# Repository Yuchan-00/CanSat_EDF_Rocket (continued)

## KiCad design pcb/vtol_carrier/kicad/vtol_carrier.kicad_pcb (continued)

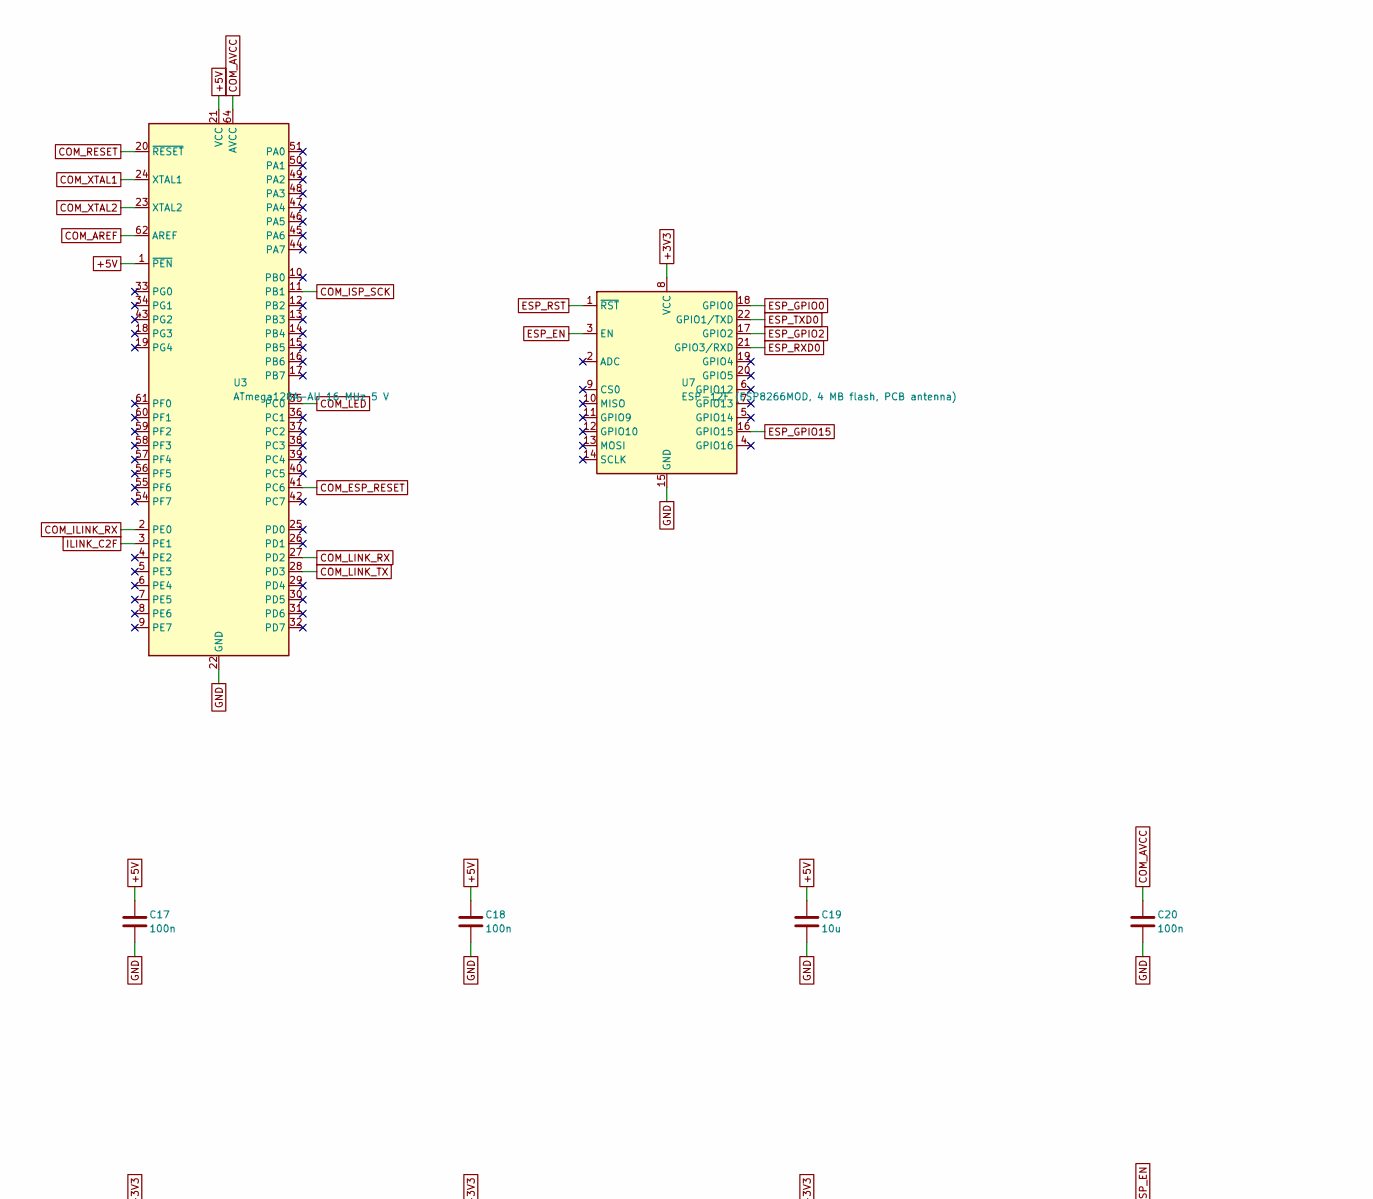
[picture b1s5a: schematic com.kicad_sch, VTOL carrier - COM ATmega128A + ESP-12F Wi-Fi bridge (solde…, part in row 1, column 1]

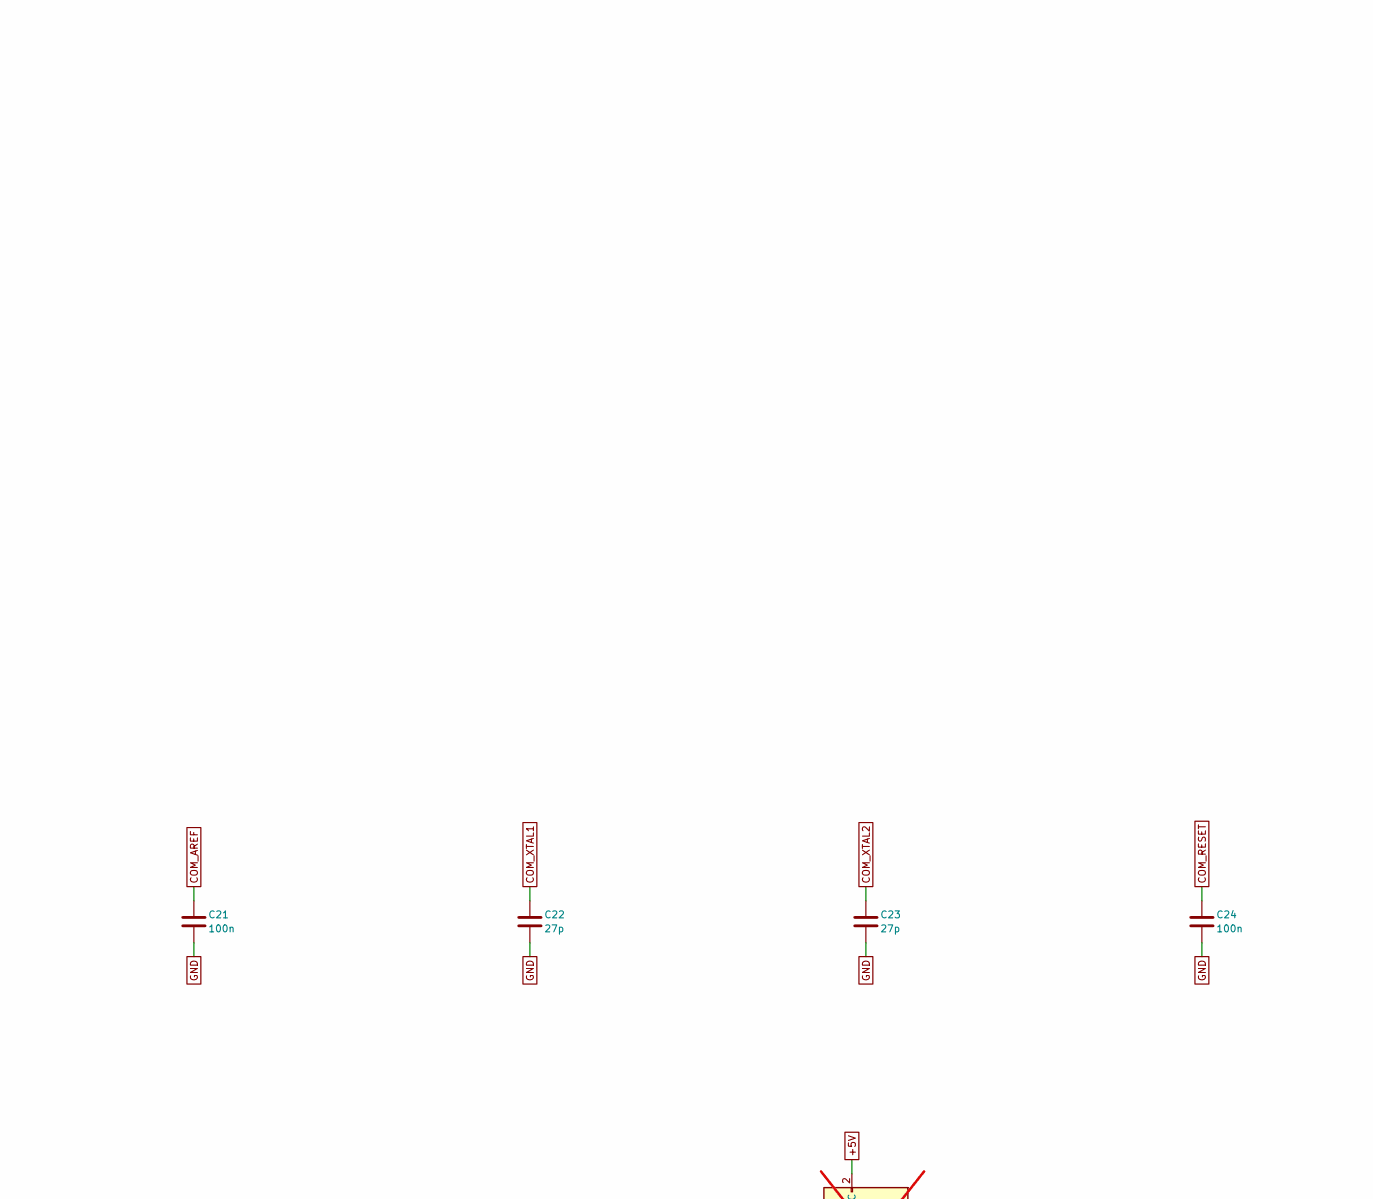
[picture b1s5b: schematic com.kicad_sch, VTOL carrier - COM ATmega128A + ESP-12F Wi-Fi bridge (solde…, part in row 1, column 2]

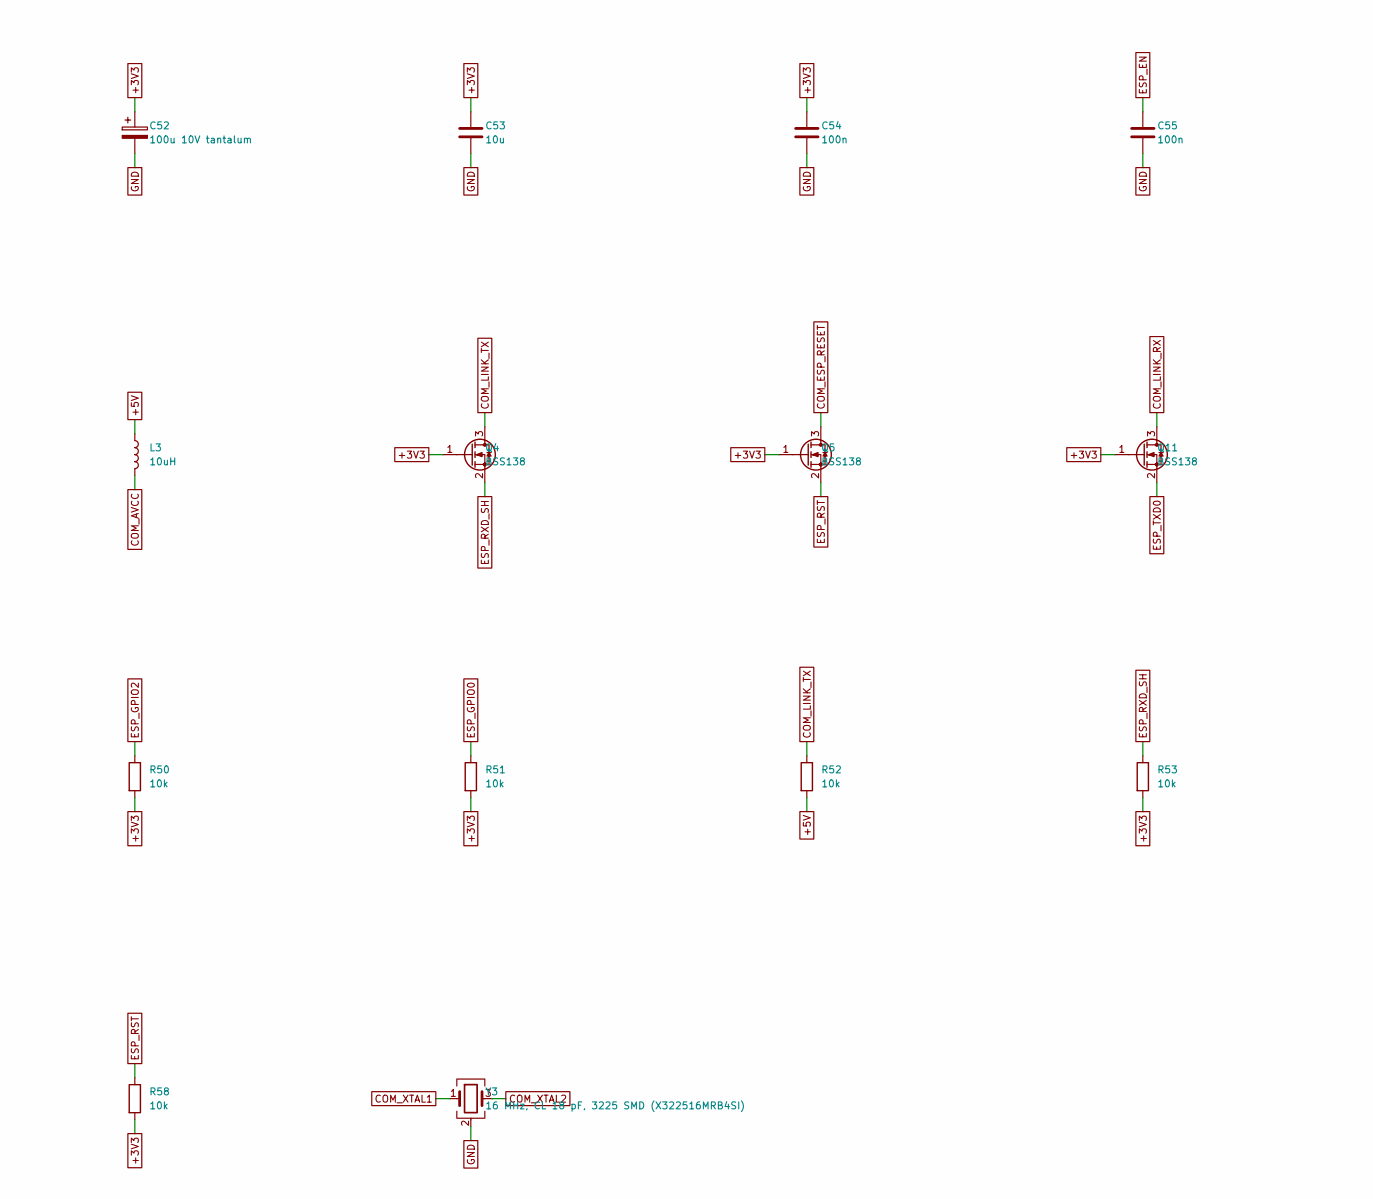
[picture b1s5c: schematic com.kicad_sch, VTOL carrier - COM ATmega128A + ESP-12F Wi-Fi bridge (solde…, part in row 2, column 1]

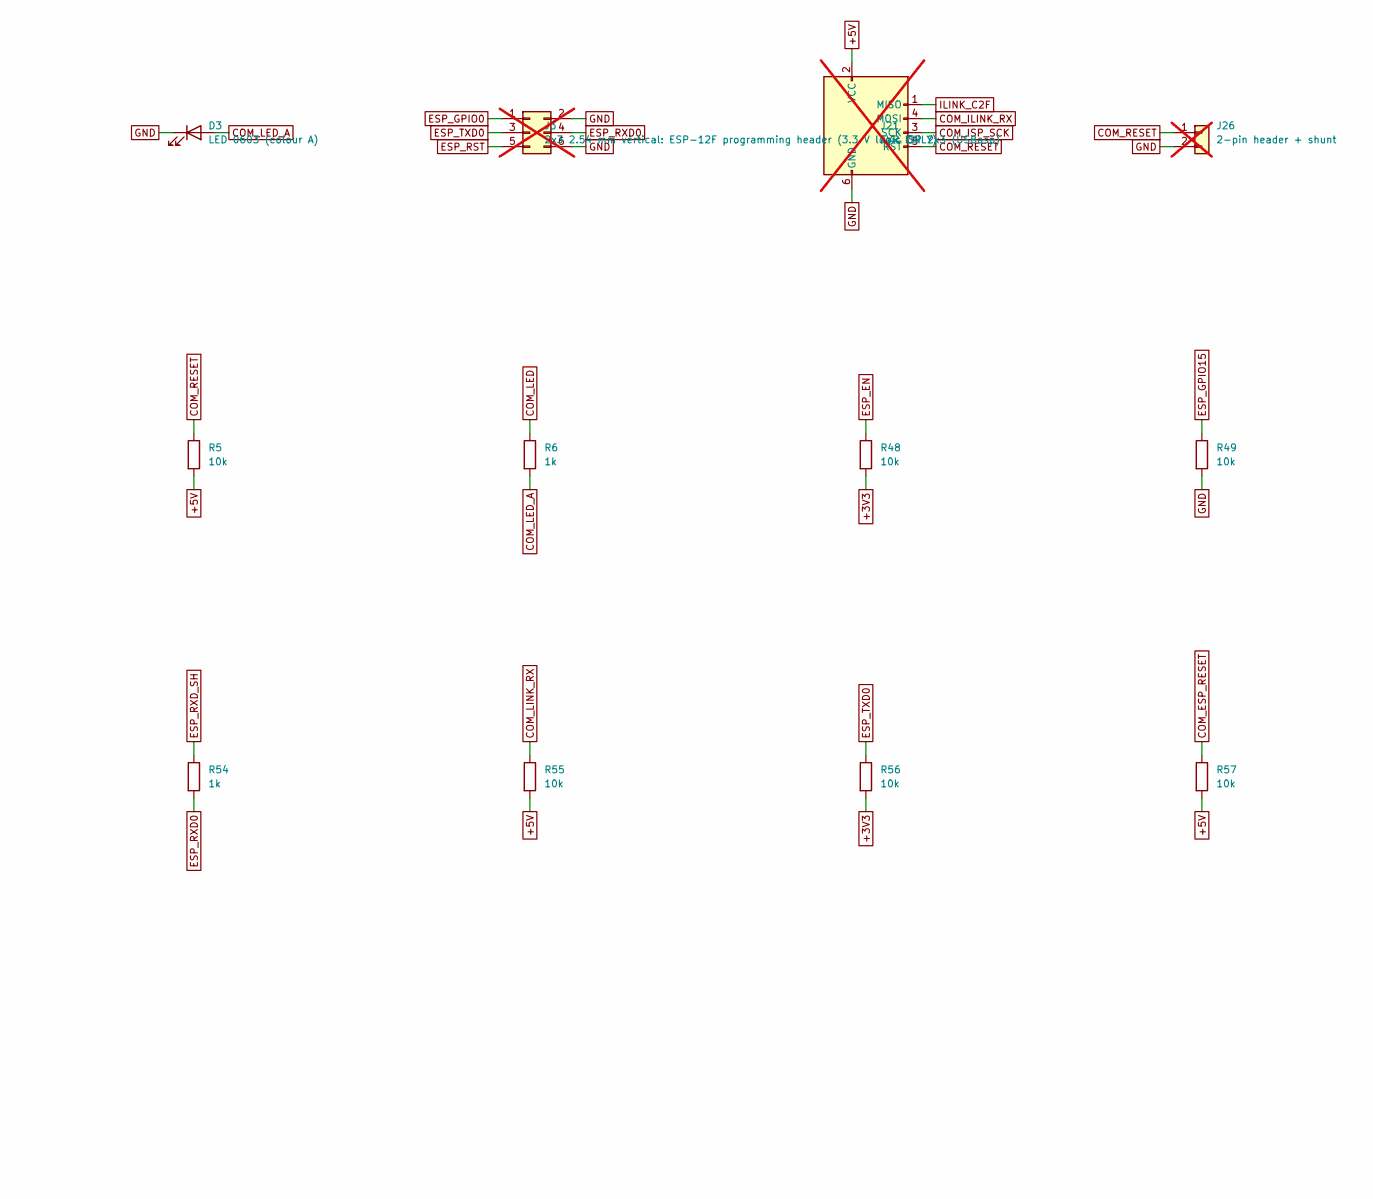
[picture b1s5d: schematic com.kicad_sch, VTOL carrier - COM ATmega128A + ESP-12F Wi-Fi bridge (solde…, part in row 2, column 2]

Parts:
C17, C18, C20, C54: 100n; C_0402_1005Metric
C19, C53: 10u; C_0805_2012Metric
C21, C24, C55: 100n; C_0603_1608Metric
C22, C23: 27p; C_0402_1005Metric
C52: 100u 10V tantalum; CP_EIA-3528-21_Kemet-B
D3: LED 0603 (colour A); LED_0603_1608Metric
J3: 2x3 2.54 mm vertical: ESP-12F programming header 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; PinHeader_2x03_P2.54mm_Vertical; not fitted
J21: AVR ISP 2x3 (USBasp); PinHeader_2x03_P2.54mm_Vertical; not fitted
J26: 2-pin header + shunt; PinHeader_1x02_P2.54mm_Vertical; not fitted
L3: 10uH; L_0805_2012Metric
Q4, Q5, Q11: BSS138; SOT-23
R5, R48, R49, R50, R51, R52, R53, R55, R56, R57, R58: 10k; R_0603_1608Metric
R6, R54: 1k; R_0603_1608Metric
U3: ATmega128A-AU 16 MHz 5 V; TQFP-64_14x14mm_P0.8mm
U7: ESP-12F (ESP8266MOD, 4 MB flash, PCB antenna); ESP-12E
Y3: 16 MHz, CL 18 pF, 3225 SMD (X322516MRB4SI); Crystal_SMD_3225-4Pin_3.2x2.5mm

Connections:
+3V3: C52.1, C53.1, C54.1, Q4.1 (G), Q5.1 (G), Q11.1 (G), R48.2, R50.2, R51.2, R53.2, R56.2, R58.2, U7.8 (VCC); also elsewhere on the board
+5V: C17.1, C18.1, C19.1, J21.2 (VCC), L3.1, R5.2, R52.2, R55.2, R57.2, U3.1 (~PEN), U3.21 (VCC), U3.52 (VCC); also elsewhere on the board
COM_AREF: C21.1, U3.62 (AREF)
COM_AVCC: C20.1, L3.2, U3.64 (AVCC)
COM_ESP_RESET: Q5.3 (D), R57.1, U3.41 (PC6)
COM_ILINK_RX: J21.4 (MOSI), U3.2 (PE0); also elsewhere on the board
COM_ISP_SCK: J21.3 (SCK), U3.11 (PB1)
COM_LED: R6.1, U3.35 (PC0)
COM_LED_A: D3.2 (A), R6.2
COM_LINK_RX: Q11.3 (D), R55.1, U3.27 (PD2)
COM_LINK_TX: Q4.3 (D), R52.1, U3.28 (PD3)
COM_RESET: C24.1, J21.5 (~RST), J26.1, R5.1, U3.20 (~RESET)
COM_XTAL1: C22.1, U3.24 (XTAL1), Y3.1
COM_XTAL2: C23.1, U3.23 (XTAL2), Y3.3
ESP_EN: C55.1, R48.1, U7.3 (EN)
ESP_GPIO0: J3.1, R51.1, U7.18 (GPIO0)
ESP_GPIO2: R50.1, U7.17 (GPIO2)
ESP_GPIO15: R49.1, U7.16 (GPIO15)
ESP_RST: J3.5, Q5.2 (S), R58.1, U7.1 (~RST)
ESP_RXD0: J3.4, R54.2, U7.21 (GPIO3/RXD)
ESP_RXD_SH: Q4.2 (S), R53.1, R54.1
ESP_TXD0: J3.3, Q11.2 (S), R56.1, U7.22 (GPIO1/TXD)
GND: C17.2, C18.2, C19.2, C20.2, C21.2, C22.2, C23.2, C24.2, C52.2, C53.2, C54.2, C55.2, D3.1 (K), J3.2, J3.6, J21.6 (GND), J26.2, R49.2, U3.22 (GND), U3.53 (GND), U3.63 (GND), U7.15 (GND), Y3.2 (G), Y3.4 (G); also elsewhere on the board
ILINK_C2F: J21.1 (MISO), U3.3 (PE1); also elsewhere on the board

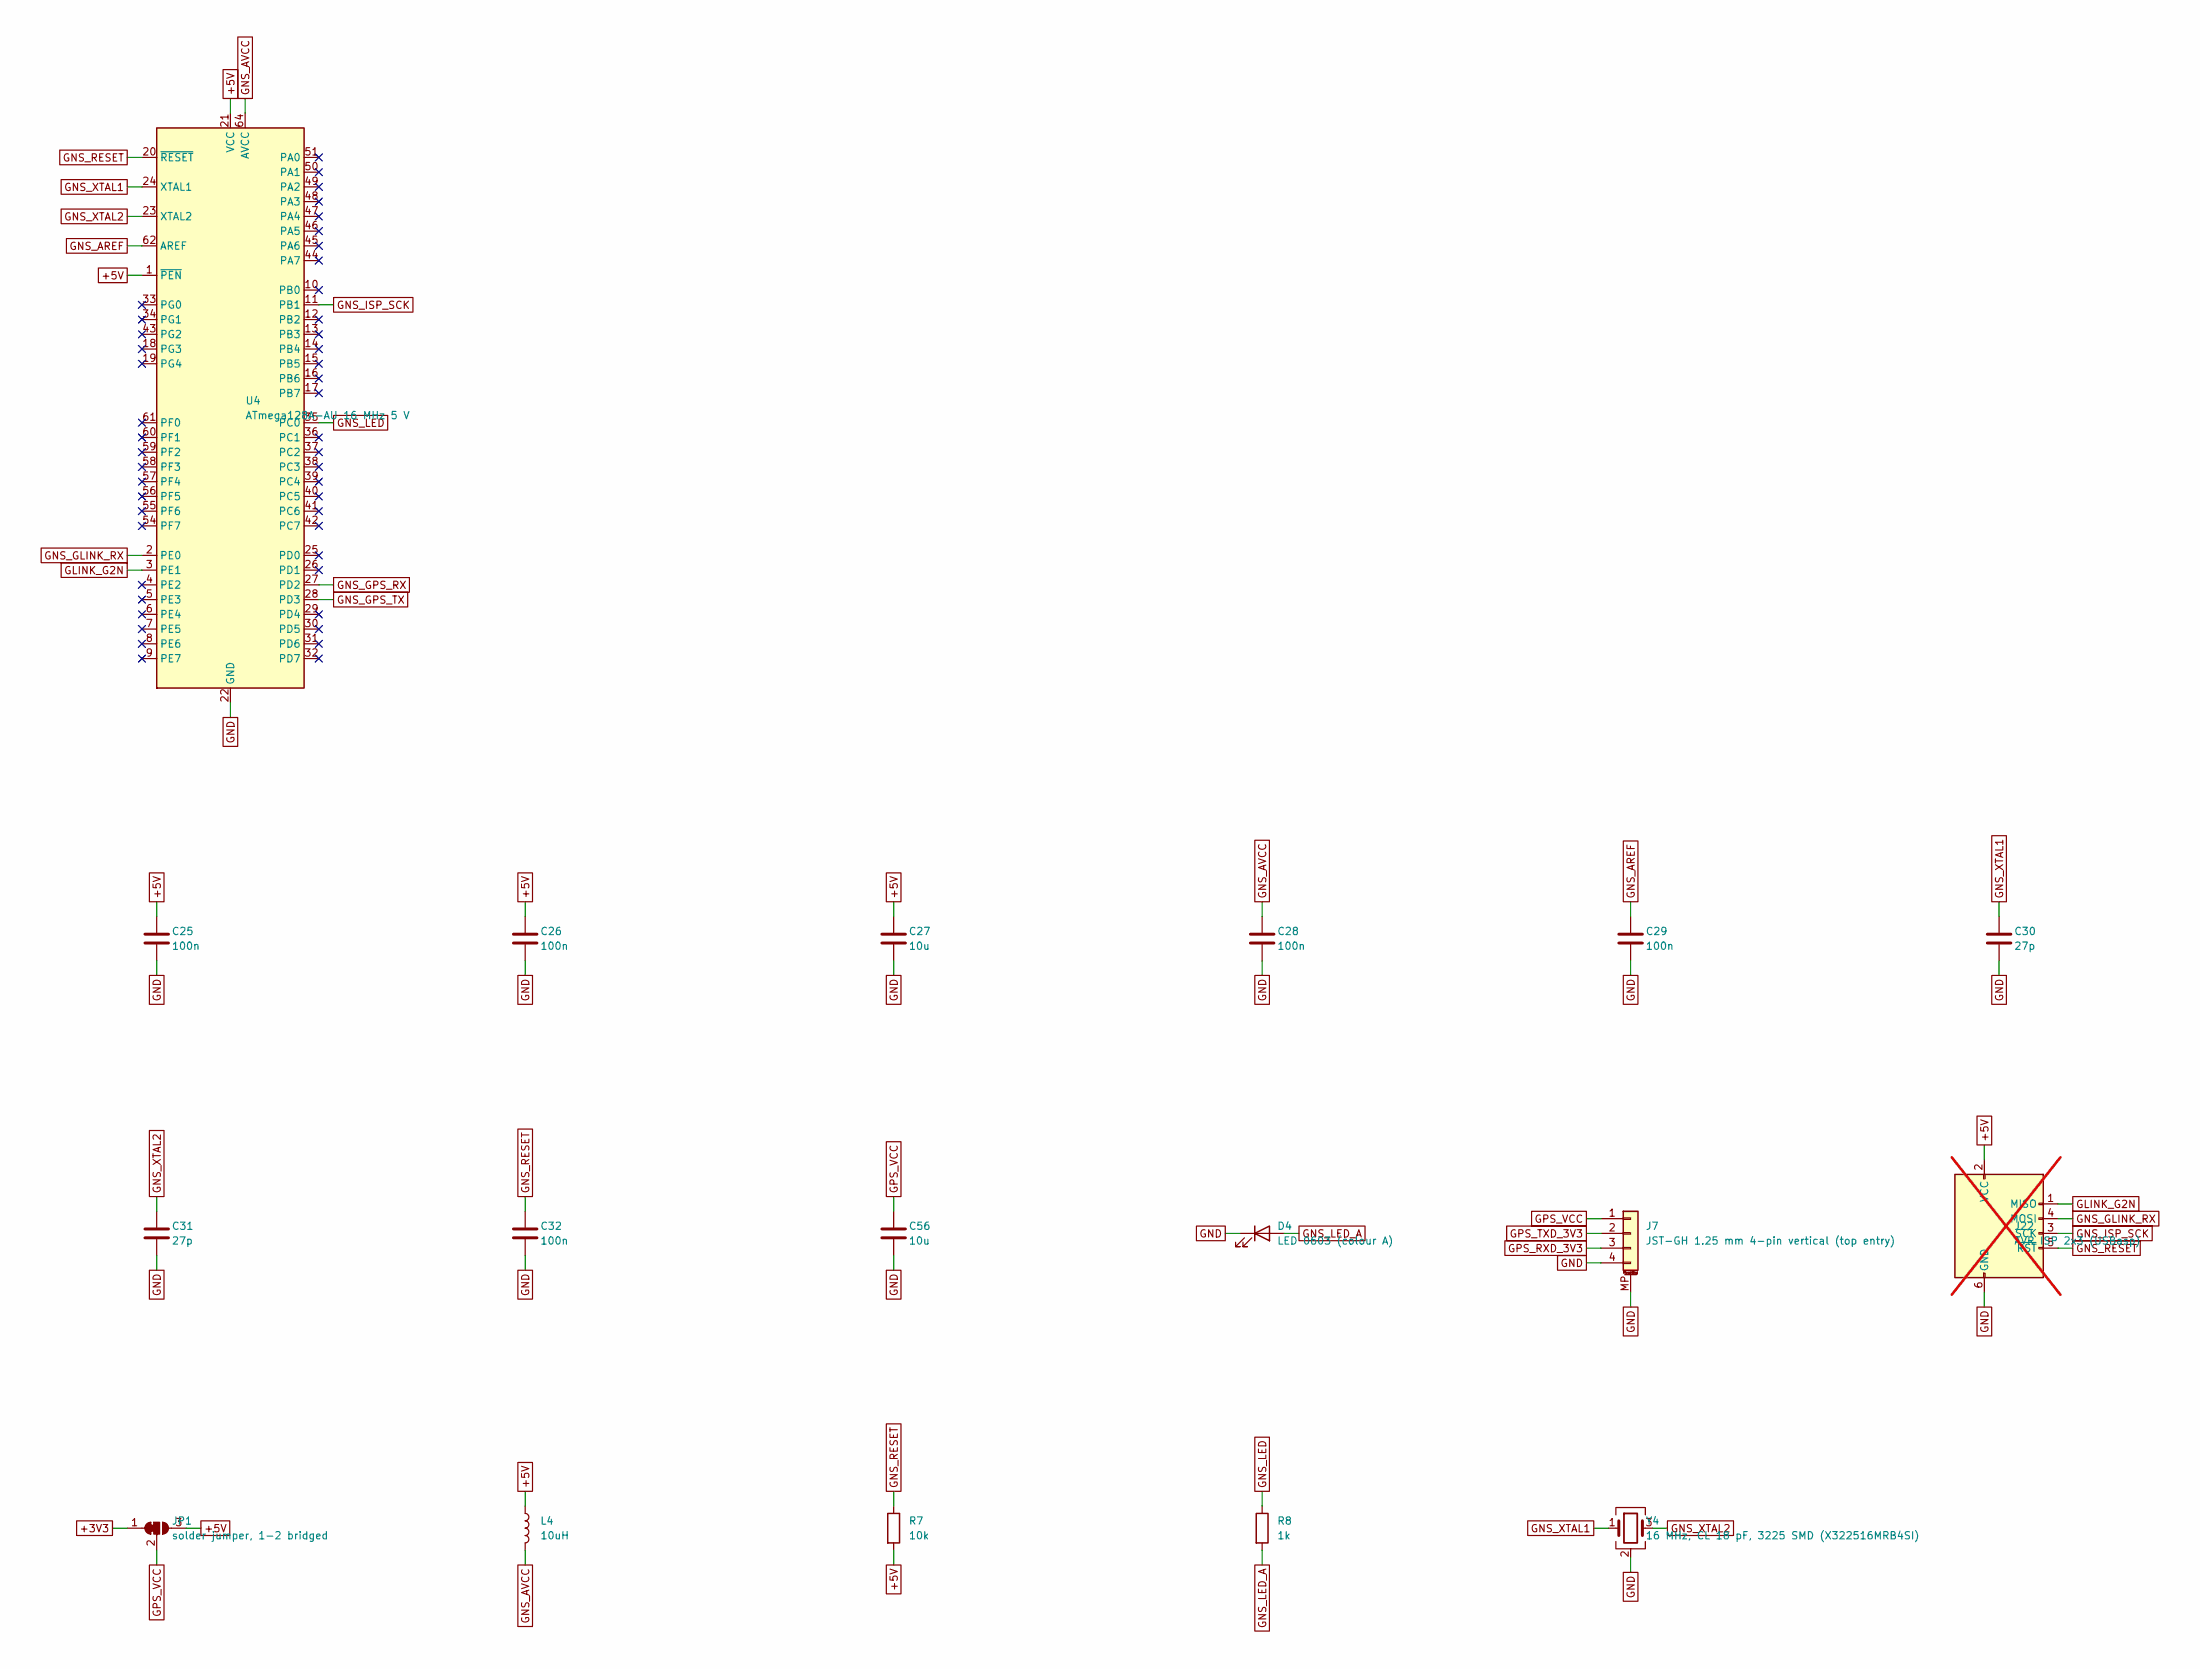
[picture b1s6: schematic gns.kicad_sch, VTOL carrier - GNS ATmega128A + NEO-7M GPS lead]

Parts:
C25, C26, C28: 100n; C_0402_1005Metric
C27, C56: 10u; C_0805_2012Metric
C29, C32: 100n; C_0603_1608Metric
C30, C31: 27p; C_0402_1005Metric
D4: LED 0603 (colour A); LED_0603_1608Metric
J7: JST-GH 1.25 mm 4-pin vertical (top entry); JST_GH_BM04B-GHS-TBT_1x04-1MP_P1.25mm_Vertical
J22: AVR ISP 2x3 (USBasp); PinHeader_2x03_P2.54mm_Vertical; not fitted
JP1: solder jumper, 1-2 bridged; SolderJumper-3_P1.3mm_Bridged12_RoundedPad1.0x1.5mm
L4: 10uH; L_0805_2012Metric
R7: 10k; R_0603_1608Metric
R8: 1k; R_0603_1608Metric
U4: ATmega128A-AU 16 MHz 5 V; TQFP-64_14x14mm_P0.8mm
Y4: 16 MHz, CL 18 pF, 3225 SMD (X322516MRB4SI); Crystal_SMD_3225-4Pin_3.2x2.5mm

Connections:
+3V3: JP1.1 (A); also elsewhere on the board
+5V: C25.1, C26.1, C27.1, J22.2 (VCC), JP1.3 (B), L4.1, R7.2, U4.1 (~PEN), U4.21 (VCC), U4.52 (VCC); also elsewhere on the board
GLINK_G2N: J22.1 (MISO), U4.3 (PE1); also elsewhere on the board
GND: C25.2, C26.2, C27.2, C28.2, C29.2, C30.2, C31.2, C32.2, C56.2, D4.1 (K), J7.4, J7.MP (MountPin), J22.6 (GND), U4.22 (GND), U4.53 (GND), U4.63 (GND), Y4.2 (G), Y4.4 (G); also elsewhere on the board
GNS_AREF: C29.1, U4.62 (AREF)
GNS_AVCC: C28.1, L4.2, U4.64 (AVCC)
GNS_GLINK_RX: J22.4 (MOSI), U4.2 (PE0); also elsewhere on the board
GNS_GPS_RX: U4.27 (PD2); also elsewhere on the board
GNS_GPS_TX: U4.28 (PD3); also elsewhere on the board
GNS_ISP_SCK: J22.3 (SCK), U4.11 (PB1)
GNS_LED: R8.1, U4.35 (PC0)
GNS_LED_A: D4.2 (A), R8.2
GNS_RESET: C32.1, J22.5 (~RST), R7.1, U4.20 (~RESET)
GNS_XTAL1: C30.1, U4.24 (XTAL1), Y4.1
GNS_XTAL2: C31.1, U4.23 (XTAL2), Y4.3
GPS_RXD_3V3: J7.3; also elsewhere on the board
GPS_TXD_3V3: J7.2; also elsewhere on the board
GPS_VCC: C56.1, J7.1, JP1.2 (C)

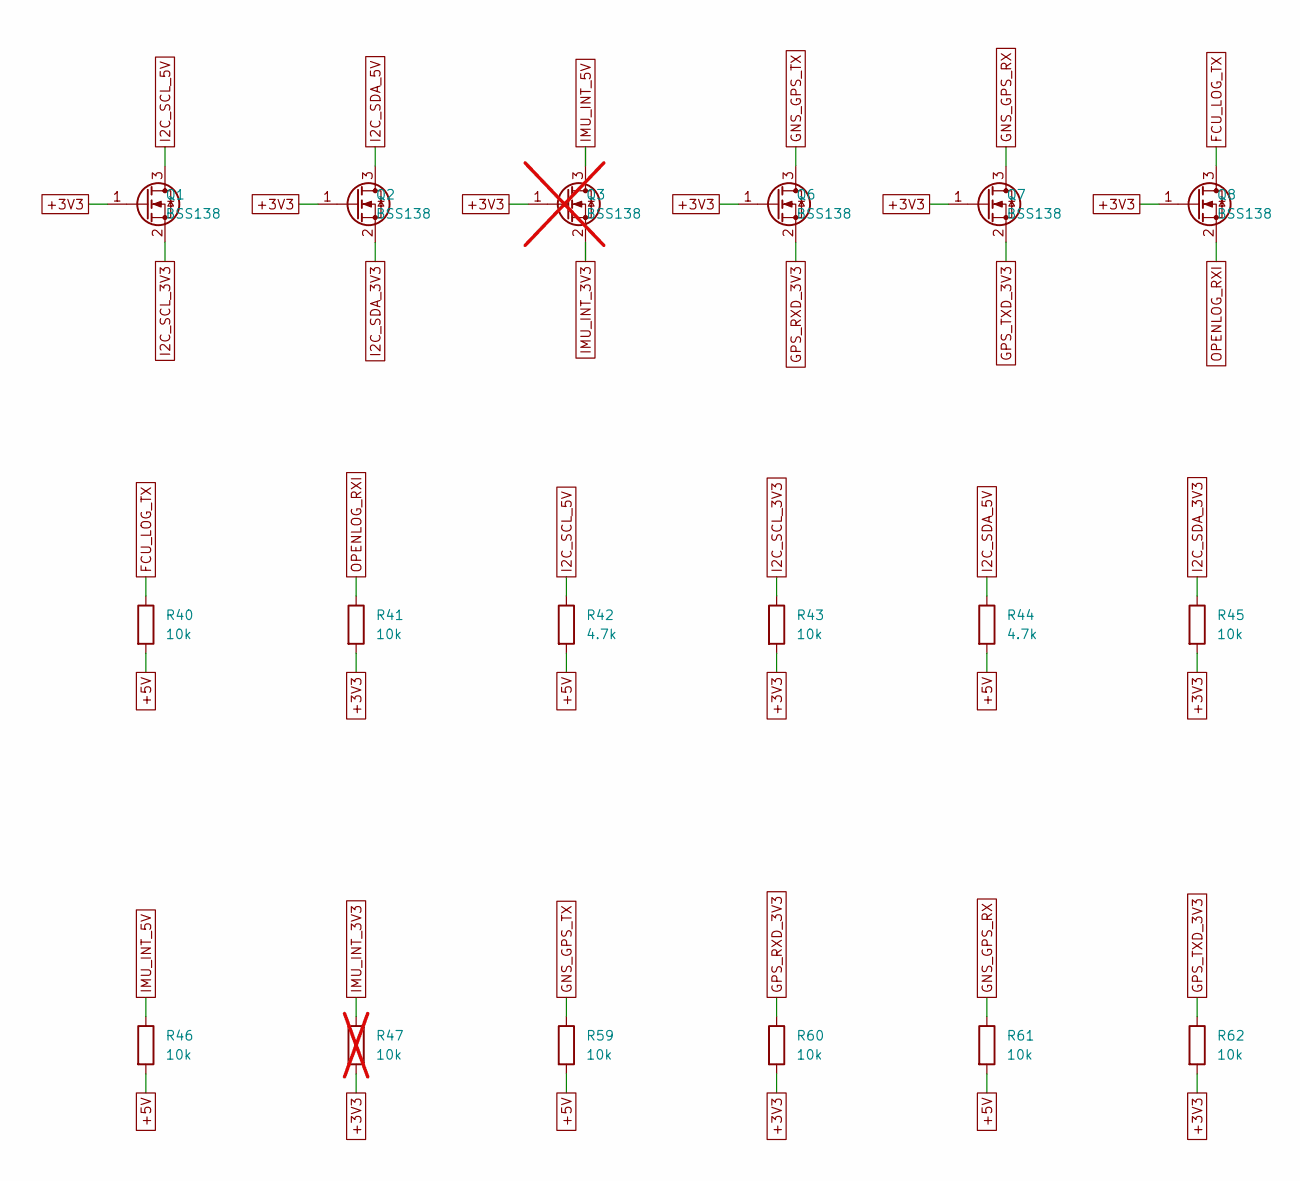
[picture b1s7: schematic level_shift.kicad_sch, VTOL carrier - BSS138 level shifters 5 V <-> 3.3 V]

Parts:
Q1, Q2, Q6, Q7, Q8: BSS138; SOT-23
Q3: BSS138; SOT-23; not fitted
R40, R41, R43, R45, R46, R59, R60, R61, R62: 10k; R_0603_1608Metric
R42, R44: 4.7k; R_0603_1608Metric
R47: 10k; R_0603_1608Metric; not fitted

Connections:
+3V3: Q1.1 (G), Q2.1 (G), Q3.1 (G), Q6.1 (G), Q7.1 (G), Q8.1 (G), R41.2, R43.2, R45.2, R47.2, R60.2, R62.2; also elsewhere on the board
+5V: R40.2, R42.2, R44.2, R46.2, R59.2, R61.2; also elsewhere on the board
FCU_LOG_TX: Q8.3 (D), R40.1; also elsewhere on the board
GNS_GPS_RX: Q7.3 (D), R61.1; also elsewhere on the board
GNS_GPS_TX: Q6.3 (D), R59.1; also elsewhere on the board
GPS_RXD_3V3: Q6.2 (S), R60.1; also elsewhere on the board
GPS_TXD_3V3: Q7.2 (S), R62.1; also elsewhere on the board
I2C_SCL_3V3: Q1.2 (S), R43.1; also elsewhere on the board
I2C_SCL_5V: Q1.3 (D), R42.1; also elsewhere on the board
I2C_SDA_3V3: Q2.2 (S), R45.1; also elsewhere on the board
I2C_SDA_5V: Q2.3 (D), R44.1; also elsewhere on the board
IMU_INT_3V3: Q3.2 (S), R47.1; also elsewhere on the board
IMU_INT_5V: Q3.3 (D), R46.1; also elsewhere on the board
OPENLOG_RXI: Q8.2 (S), R41.1; also elsewhere on the board

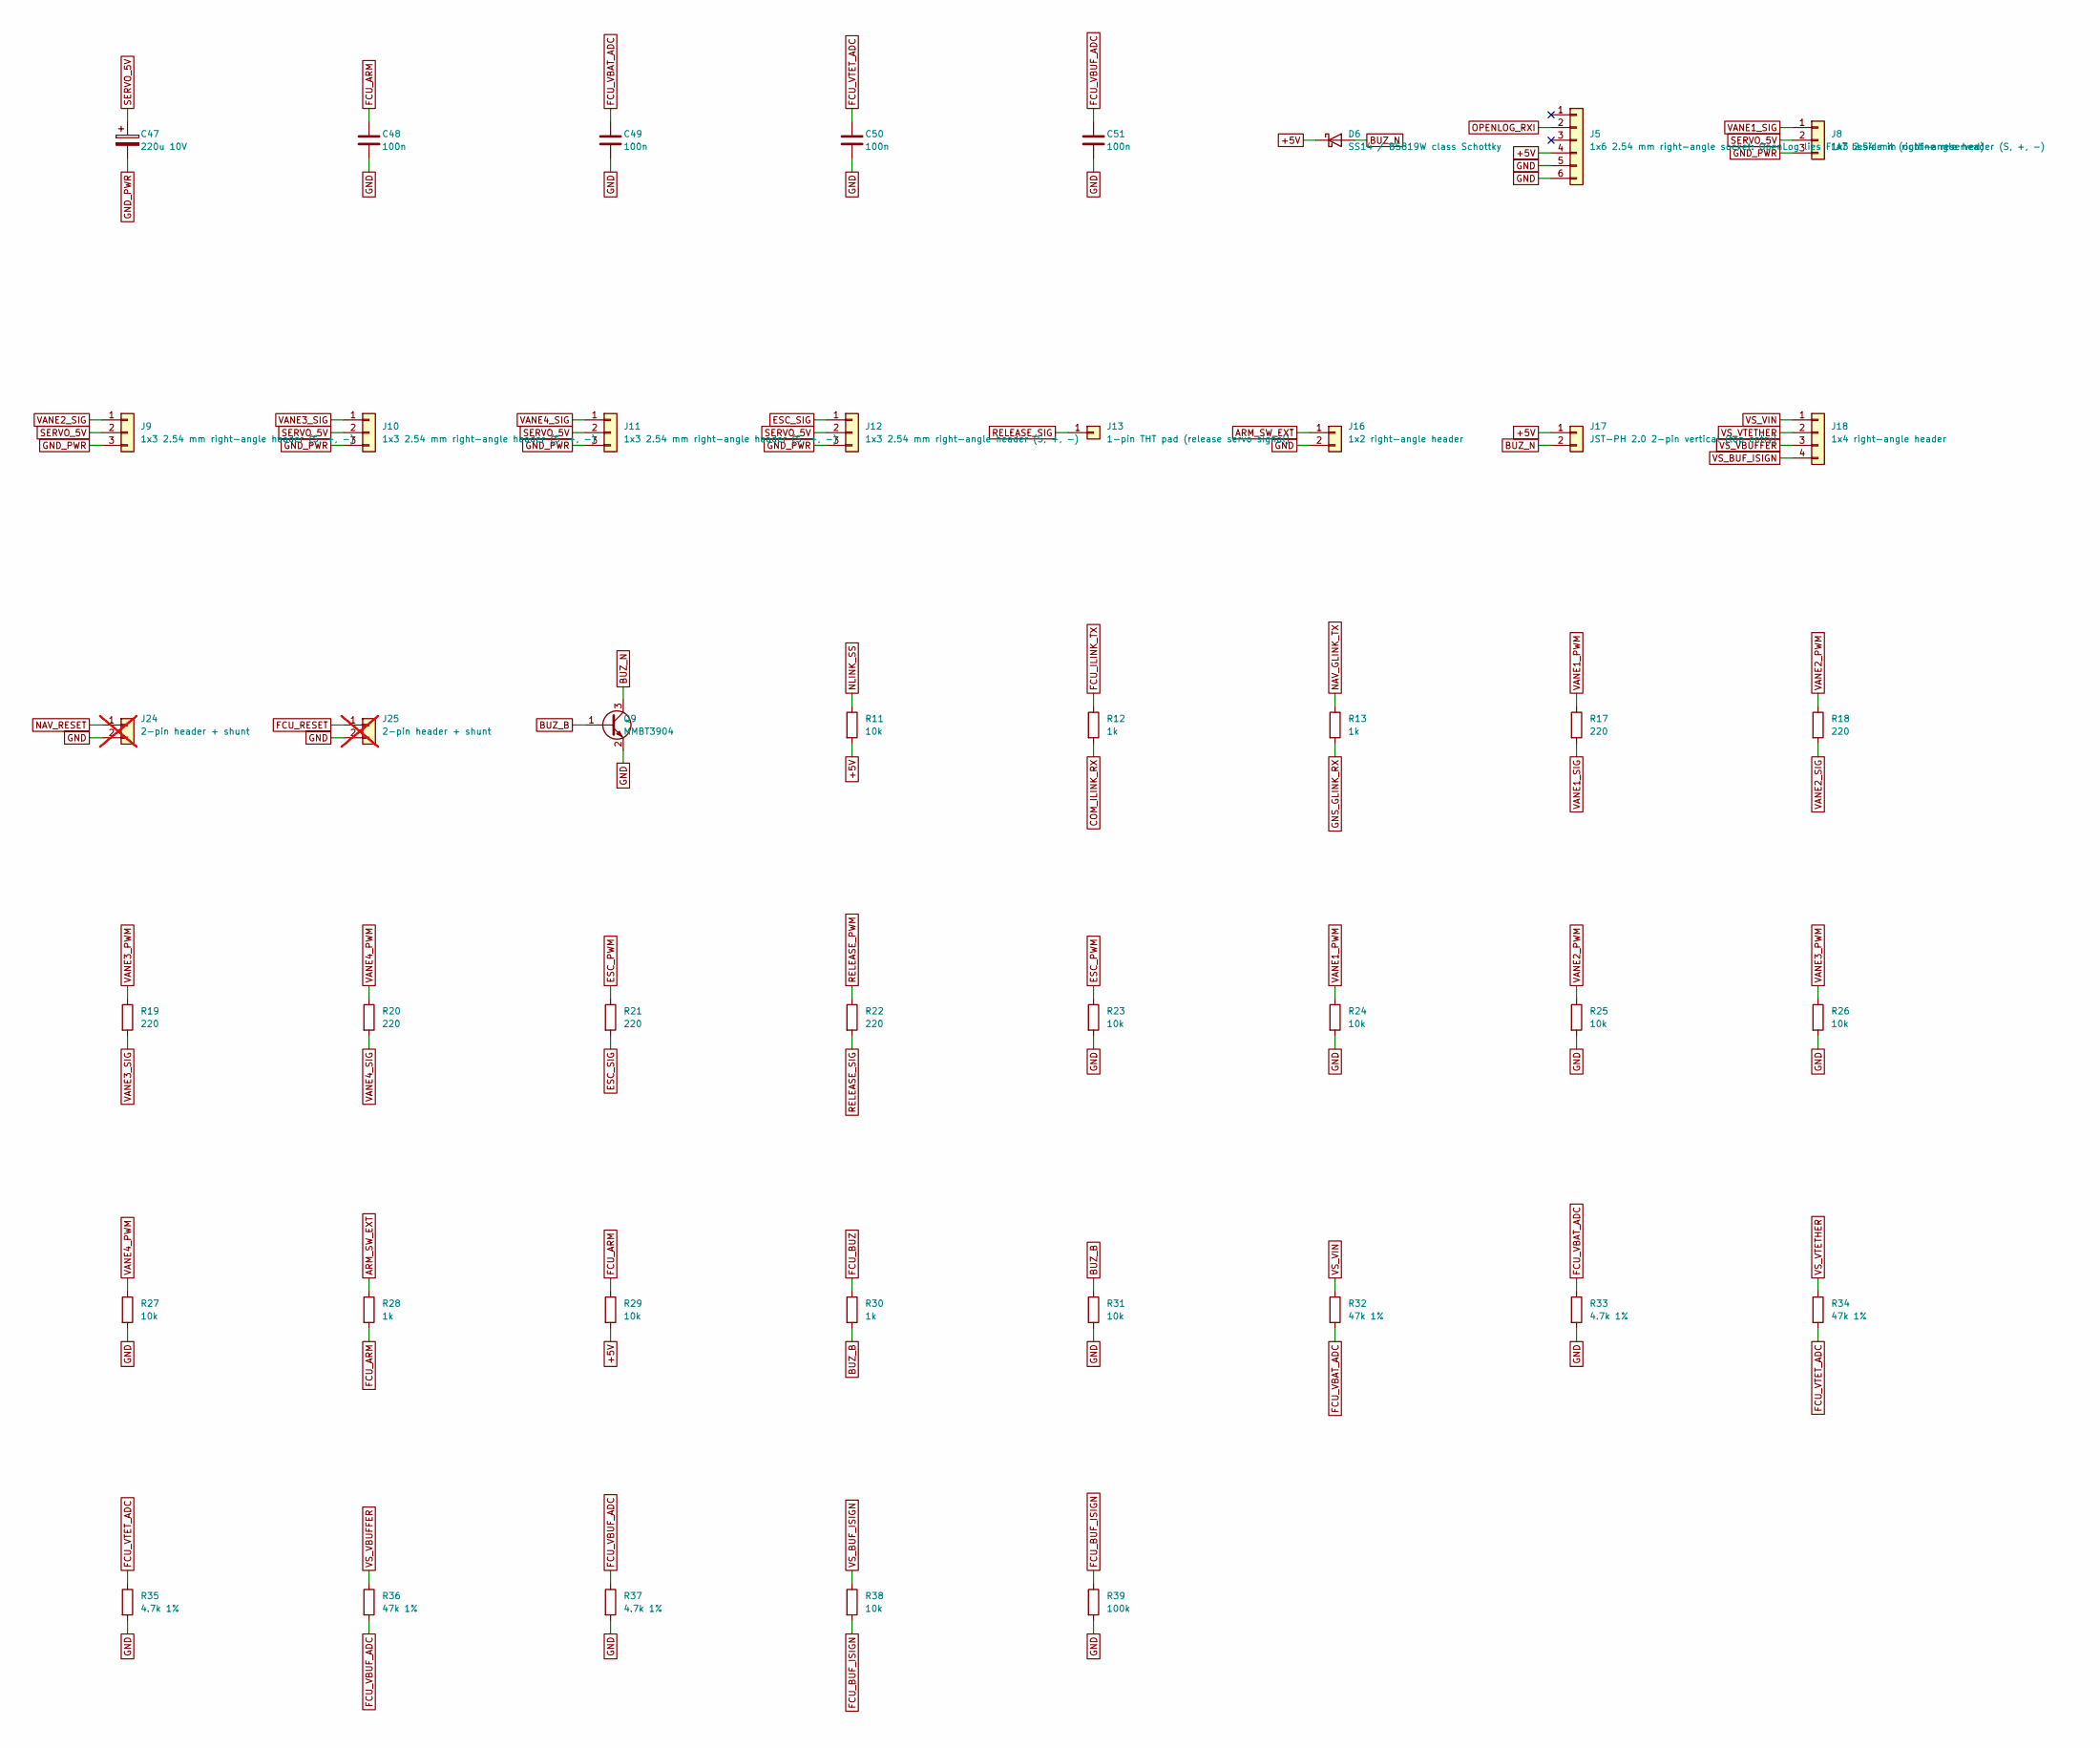
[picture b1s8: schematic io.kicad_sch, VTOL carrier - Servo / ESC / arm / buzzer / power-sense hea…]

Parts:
C47: 220u 10V; CP_Elec_6.3x5.4
C48, C49, C50, C51: 100n; C_0603_1608Metric
D6: SS14 / B5819W class Schottky; D_SOD-123
J5: 1x6 2.54 mm right-angle socket: OpenLog lies FLAT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; PinSocket_1x06_P2.54mm_Horizontal
J8, J9, J10, J11, J12: 1x3 2.54 mm right-angle header (S, +, -); PinHeader_1x03_P2.54mm_Horizontal
J13: 1-pin THT pad (release servo signal); TestPoint_THTPad_D2.0mm_Drill1.0mm
J16: 1x2 right-angle header; PinHeader_1x02_P2.54mm_Horizontal
J17: JST-PH 2.0 2-pin vertical (top entry); JST_PH_B2B-PH-K_1x02_P2.00mm_Vertical
J18: 1x4 right-angle header; PinHeader_1x04_P2.54mm_Horizontal
J24, J25: 2-pin header + shunt; PinHeader_1x02_P2.54mm_Vertical; not fitted
Q9: MMBT3904; SOT-23
R11, R23, R24, R25, R26, R27, R29, R31, R38: 10k; R_0603_1608Metric
R12, R13, R28, R30: 1k; R_0603_1608Metric
R17, R18, R19, R20, R21, R22: 220; R_0603_1608Metric
R32, R34, R36: 47k 1%; R_0603_1608Metric
R33, R35, R37: 4.7k 1%; R_0603_1608Metric
R39: 100k; R_0603_1608Metric

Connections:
+5V: D6.1 (K), J5.4, J17.1, R11.2, R29.2; also elsewhere on the board
ARM_SW_EXT: J16.1, R28.1
BUZ_B: Q9.1 (B), R30.2, R31.1
BUZ_N: D6.2 (A), J17.2, Q9.3 (C)
COM_ILINK_RX: R12.2; also elsewhere on the board
ESC_PWM: R21.1, R23.1; also elsewhere on the board
ESC_SIG: J12.1, R21.2
FCU_ARM: C48.1, R28.2, R29.1; also elsewhere on the board
FCU_BUF_ISIGN: R38.2, R39.1; also elsewhere on the board
FCU_BUZ: R30.1; also elsewhere on the board
FCU_ILINK_TX: R12.1; also elsewhere on the board
FCU_RESET: J25.1; also elsewhere on the board
FCU_VBAT_ADC: C49.1, R32.2, R33.1; also elsewhere on the board
FCU_VBUF_ADC: C51.1, R36.2, R37.1; also elsewhere on the board
FCU_VTET_ADC: C50.1, R34.2, R35.1; also elsewhere on the board
GND: C48.2, C49.2, C50.2, C51.2, J5.5, J5.6, J16.2, J24.2, J25.2, Q9.2 (E), R23.2, R24.2, R25.2, R26.2, R27.2, R31.2, R33.2, R35.2, R37.2, R39.2; also elsewhere on the board
GND_PWR: C47.2, J8.3, J9.3, J10.3, J11.3, J12.3; also elsewhere on the board
GNS_GLINK_RX: R13.2; also elsewhere on the board
NAV_GLINK_TX: R13.1; also elsewhere on the board
NAV_RESET: J24.1; also elsewhere on the board
NLINK_SS: R11.1; also elsewhere on the board
OPENLOG_RXI: J5.2; also elsewhere on the board
RELEASE_PWM: R22.1; also elsewhere on the board
RELEASE_SIG: J13.1, R22.2
SERVO_5V: C47.1, J8.2, J9.2, J10.2, J11.2, J12.2
VANE1_PWM: R17.1, R24.1; also elsewhere on the board
VANE1_SIG: J8.1, R17.2
VANE2_PWM: R18.1, R25.1; also elsewhere on the board
VANE2_SIG: J9.1, R18.2
VANE3_PWM: R19.1, R26.1; also elsewhere on the board
VANE3_SIG: J10.1, R19.2
VANE4_PWM: R20.1, R27.1; also elsewhere on the board
VANE4_SIG: J11.1, R20.2
VS_BUF_ISIGN: J18.4, R38.1
VS_VBUFFER: J18.3, R36.1
VS_VIN: J18.1, R32.1
VS_VTETHER: J18.2, R34.1
